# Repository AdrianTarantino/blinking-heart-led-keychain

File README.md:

# Blinking Heart PCB Keychain

# Circuitry (KiCAD)

## Release v0.0.0 (df470290bcf13d91d84e4e0569294659ad3c17ab)
### What to fix
- Redesign layout strictly using metric. Setup grid settings before-hand.

- Make component placement diagram for LEDs, button and MOSFET in CAD software like FreeCAD to make
case design easier.

- CD4017BE footprint incorrect.
    - Make via larger.
    - Make pads closer.
    - Get additional IC from electronics bin at home.

- Make all resistor footprints larger.

- Add box surrounding vias of MOSFET to indicate the full size of the component.

- Make circle of LEDs footprint smaller.

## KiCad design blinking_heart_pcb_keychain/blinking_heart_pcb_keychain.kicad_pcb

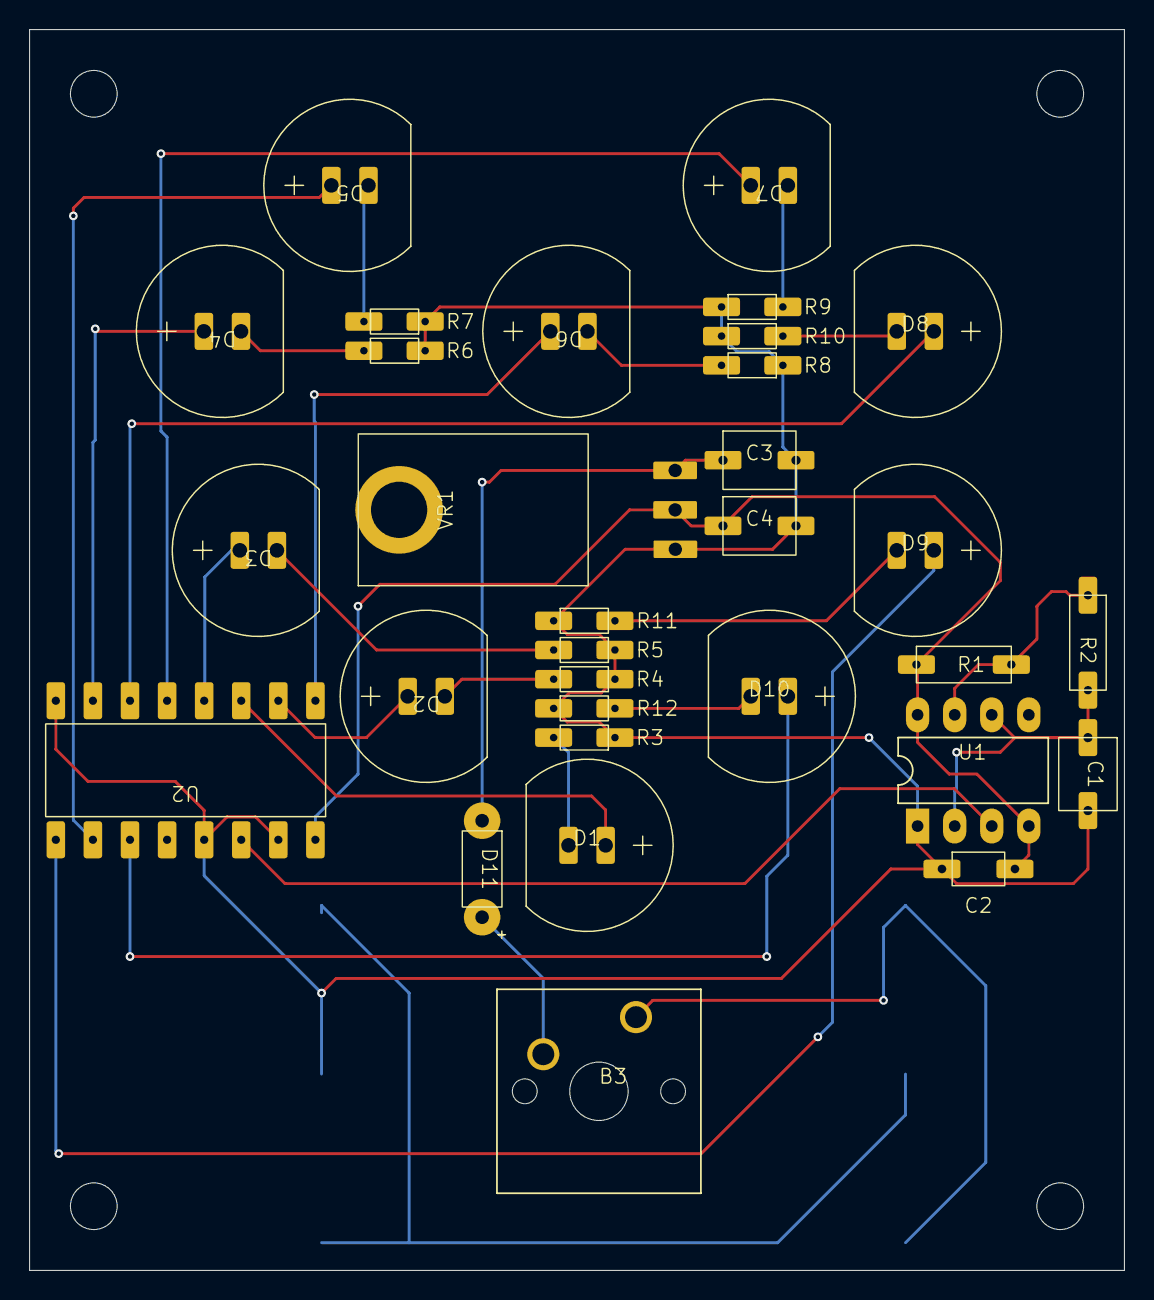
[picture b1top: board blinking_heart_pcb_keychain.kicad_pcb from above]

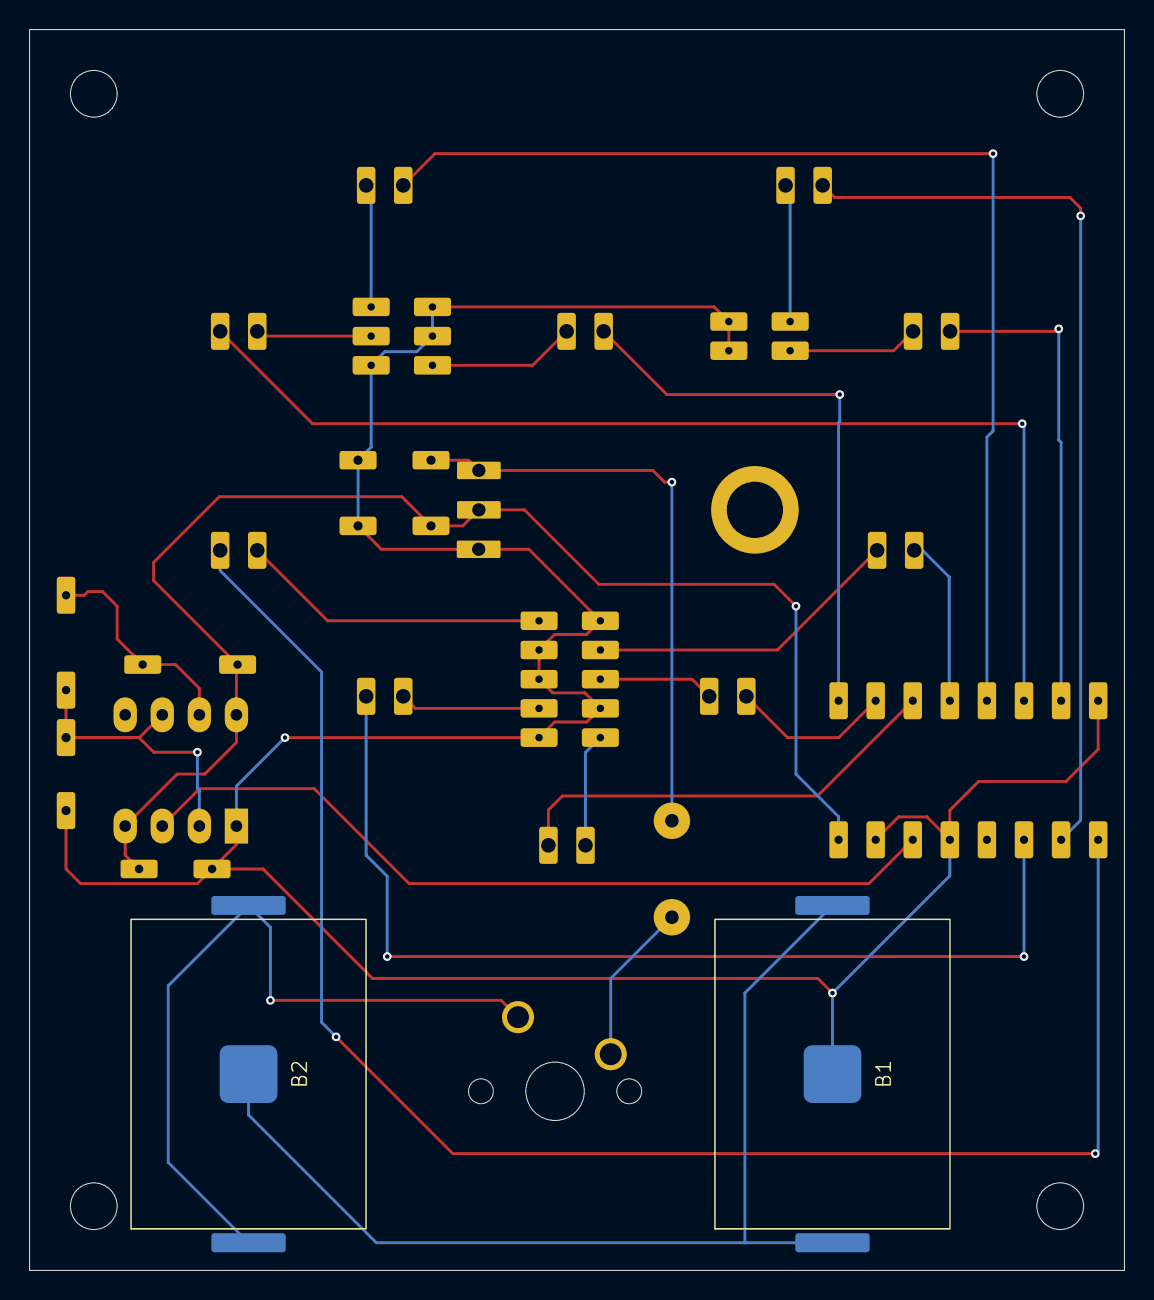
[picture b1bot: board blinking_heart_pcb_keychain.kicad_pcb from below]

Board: 2 copper layers, 75.0 x 85.0 mm, 33 parts (2 on the bottom side), 29 nets.

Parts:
B1, B2: +3V; B_CR2032
B3: MX1A-E1NW
C1, C3, C4: 100uF; C_THT_100uF
C2: 10uF; C_THT_10nF
D1, D2, D3, D4, D5, D6, D7, D8, D9, D10: LED_THT_RED
D11: D_1N5817
R1: 1KΩ; R THT 1KΩ
R2: 6.8KΩ; R THT 1KΩ
R3, R4, R5, R6, R7, R8, R9, R10, R11, R12: 130Ω; R_THT_130Ω
U1: NE555; NE555P
U2: CD4017BE
VR1: 5V; VR_5V

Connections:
+5V: C2.2, C4.1, R1.1, U1.4 (RESET), U1.8 (VCC), U2.16 (+5V), VR1.2 (VOUT)
/CLK: U1.3 (OUT), U2.14 (CLK)
GND: B1.2 (GND), C1.2, C2.1, C3.2, C4.2, R3.2, R4.2, R5.2, R6.2, R7.2, R8.2, R9.2, R10.2, R11.2, R12.2, U1.1 (GND), U2.8 (GND), U2.13 (CLK_PAUSE), U2.15 (RESET), VR1.1 (GND)
unnamed: B1.1 (+3V), B2.2 (GND)
unnamed: B2.1 (+3V), B3.1
unnamed: B3.2, D11.2
unnamed: D1.1, R3.1
unnamed: D2.1, R4.1
unnamed: D3.1, R5.1
unnamed: D4.1, R6.1
unnamed: D5.1, R7.1
unnamed: D6.1, R8.1
unnamed: D7.1, R9.1
unnamed: D8.1, R10.1
unnamed: D9.1, R11.1
unnamed: D10.1, R12.1
unnamed: R1.2, R2.1, U1.7 (DISCH)
unnamed: C1.1, R2.2, U1.2 (TRIG), U1.6 (THRES)
unnamed: D1.2, U2.3 (OUT_0)
unnamed: D2.2, U2.2 (OUT_1)
unnamed: D3.2, U2.4 (OUT_2)
unnamed: D4.2, U2.7 (OUT_3)
unnamed: D5.2, U2.10 (OUT_4)
unnamed: D6.2, U2.1 (OUT_5)
unnamed: D7.2, U2.5 (OUT_6)
unnamed: D8.2, U2.6 (OUT_7)
unnamed: D9.2, U2.9 (OUT_8)
unnamed: D10.2, U2.11 (OUT_9)
unnamed: C3.1, D11.1, VR1.3 (VIN)

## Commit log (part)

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2026-06-12 Making 555 IC component
2026-06-12 Making more changes
2026-06-14 Making clock generator circuit
2026-06-14 Building counter circuit
2026-06-14 Adding power circuit to the schematic
2026-06-15 Starting layout
2026-06-15 Begining component placement
2026-06-18 Completing most of the routing
2026-06-19 Setting up all manufacturing files
2026-06-19 Moving fab files around
